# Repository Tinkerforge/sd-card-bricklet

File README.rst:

SD Card Bricklet
================

**This Bricklet is currently in development.**

This repository contains the firmware source code and the hardware design
files. The documentation generator configs can be found at
https://github.com/Tinkerforge/generators

Repository Content
------------------

software/:
 * examples/: Examples for all supported languages
 * build/: Compiled files
 * src/: Source code of firmware
 * Makefile: Makefile to build project

hardware/:
 * Contains KiCad project files and additionally schematics as PDF

datasheets/:
 * Contains datasheets for sensors and complex ICs that are used

Hardware
--------

The hardware is designed with the open source EDA Suite KiCad
(http://www.kicad.org). Before you are able to open the files,
you have to install the Tinkerforge kicad-libraries
(https://github.com/Tinkerforge/kicad-libraries). You can either clone
them directly in hardware/ or clone them in a separate folder and
symlink them into hardware/
(ln -s kicad_path/kicad-libraries project_path/hardware). After that you
can open the .pro file in hardware/ with KiCad and from there view and
modify the schematics and the PCB layout.

Software
--------

If you want to do your own Brick/Bricklet firmware development we highly
recommend that you use our build environment setup script and read the
tutorial (https://www.tinkerforge.com/en/doc/Tutorials/Tutorial_Build_Environment/Tutorial.html).

To compile the C code we recommend you to install the newest GNU Arm Embedded
Toolchain (https://launchpad.net/gcc-arm-embedded/+download).
You also need to install bricklib2 (https://github.com/Tinkerforge/bricklib2).

You can either clone it directly in software/src/ or clone it in a
separate folder and symlink it into software/src/
(ln -s bricklib_path/bricklib2 project_path/software/src/). Finally make sure to
have CMake installed (http://www.cmake.org/cmake/resources/software.html).

After that you can build the firmware by invoking make in software/.
The firmware (.zbin) can then be found in software/build/ and uploaded
with brickv (click button "Flashing" on start screen).

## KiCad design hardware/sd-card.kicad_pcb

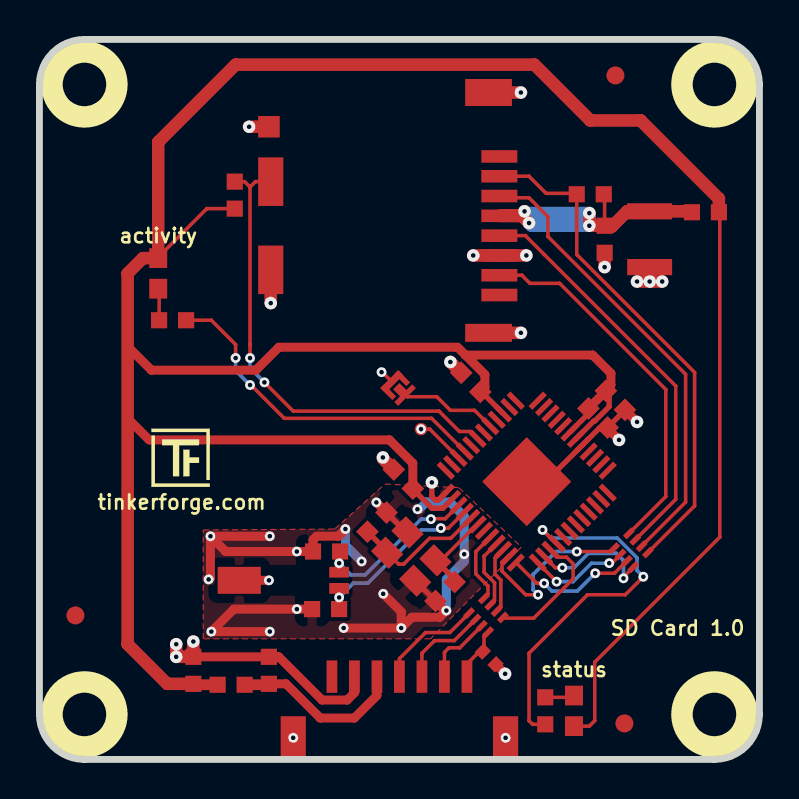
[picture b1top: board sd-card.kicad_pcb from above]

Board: 2 copper layers, 40.0 x 40.0 mm, 39 parts (0 on the bottom side), 31 nets.

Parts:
C1: 220pF; C0402F
C2, C5: 1uF; C0603F
C3, C4: 10pF; C0603F
C6, C7, C8, C11: 100nF; C0603F
C9: 220nF; C0603F
C10: 100uF; C1210
C12, C13: 15pF; C0603F
D1: blue; D0603E
D2: red; D0603E
FB1: FILTER; R0603F
Fiducial_Mark: VAL**; Fiducial_Mark
Fiducial_Mark#2, Fiducial_Mark#3: VAL**; Fiducial_Mark
J1: DM3CS; SD-Card-DM3CS
L1: FB; R0603F
P1: CON-SENSOR2
P2: BOOT; SolderJumper
P3: Debug; DEBUG_PAD
R1, R2: 10k; R0603F
R3, R4: 1k; R0603F
RP1, RP2: 82; 4X0402
U1: XMC1404; QFN48-EP2
U2, U3, U4, U5: DRILL; DRILL_NP
VAL: WEEE_7mm
VAL#2: CE_5mm
X1: 16MHz; CRYSTAL_3225
X2: 32.768kHz; AB26TRQ

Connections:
GND: C1.2, C2.1, C3.2, C4.2, C5.1, C6.2, C7.2, C8.2, C9.2, C10.2, C11.2, C12.1, C13.1, J1.6, J1.S, P1.2, P1.EP, P2.1, U1.17, U1.37, U1.EP, X1.3, X2.3
unnamed: C1.1, P1.7, RP1.4
unnamed: C2.2, FB1.1, P1.3
unnamed: C3.1, U1.41, X1.2
unnamed: C4.1, U1.42, X1.1
unnamed: C10.1, C11.1, J1.4, L1.1, R2.2
unnamed: D1.2, R4.1
unnamed: D2.2, R3.1
unnamed: J1.2, R2.1, RP2.1
unnamed: J1.3, RP2.2
unnamed: J1.5, RP2.3
unnamed: J1.7, RP2.4
unnamed: P1.4, RP1.1
unnamed: P1.5, RP1.2
unnamed: P1.6, RP1.3
unnamed: P2.2, U1.29
unnamed: P3.1, U1.34
unnamed: R3.2, U1.33
unnamed: R4.2, U1.4
RTC-XTAL1: C13.2, U1.39, X2.2
RTC-XTAL2: C12.2, U1.40, X2.1
S-CLK: RP1.7, U1.45
S-CS: RP1.8, U1.44
S-MISO: RP1.5, U1.3
S-MOSI: RP1.6, U1.46
SD-CDS: J1.CDS, R1.1, U1.31
SD-CLK: RP2.6, U1.1
SD-CS: RP2.8, U1.2
SD-MISO: RP2.5, U1.47
SD-MOSI: RP2.7, U1.48
VCC: C5.2, C6.1, C7.1, C8.1, C9.1, D1.1, D2.1, FB1.2, L1.2, R1.2, U1.18, U1.19, U1.27, U1.38

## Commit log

2022-02-25 Add initial auto-generated firmware stub for SD Card Bricklet
2022-03-24 add sd card bricklet 1.0
2022-03-24 add missing file
2022-03-24 drc check
2022-03-24 Add initial sd card with fatfs support
    sdmmc support is based on code generated by Infineon DAVE IDE.
    The FatFs library is updated to newest version.
    Currently only sd card read/write test code is run.
2022-07-06 Add license files.
2025-10-04 Fix compatibility with new Docker build image (GCC 14.2.1)

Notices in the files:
hardware/sd-card.kicad_pcb:
Licensed under CERN OHL v.1.1
Copyright (©) 2022, B.Nordmeyer
Copyright Tinkerforge GmbH 2022.
This documentation describes Open Hardware and is licensed under the
CERN OHL v. 1.1.
